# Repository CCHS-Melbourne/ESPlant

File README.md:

ESPlant - Environment Sensor Plant
=============

Welcome to the linux.conf.au Open Hardware Project.  You can see information about this and other MiniConfs at http://www.openhardwareconf.org/wiki/Main_Page

The ESPlant kit is designed to provide an open source platform to transmit environmental data to a central source using the power of wifi.

Assembled PCB:

Prototype board in action (before significant changes):

Check out a video of pick-n-placing components of the boards you'll be getting at LCA 2016.
https://www.youtube.com/watch?v=282qku2C4xo

FEATURES
--------

* ESP8266 WiFi enabled microcontroller. You can program it via the Arduino IDE, or alternatively Espressif SDK or esp-open-rtos.
* Secondary microcontroller (STM32F042) acts as USB/Serial interface and i2c Analog to Digital Converter
* Battery holder for 16340 sized 3.7V lithium cell
* Lithium battery charger interface (solar input friendly)
* Board automatically switches power source between solar input, battery, and USB power as applicable.

## Onboard Sensors (on I2C bus)

* BME280 Temperature/Humidity/Barometric Pressure sensor
* ADXL345 accelerometer

## External Sensors (all optional, connected to screw terminals)

* 2x soil moisture sensors (via ADC pins)
* DS18B20 connected to GPIO 12.
* PIR (infrared motion) sensor connected to GPIO 15.
* WS2812B LED strip connected to GPIO 13 (mislabelled as 15 on V1.3 PCB!)

The 3.3V "VSens" power rail is switchable on/off by the microcontroller. It defaults to unpowered (off). The GPIO to use is 14, and it is active low (ie driving the output low turns VSens on, driving it high turns it off).

Assembly Steps
--------------

[Assembly guide on the wiki](https://github.com/CCHS-Melbourne/ESPlant/wiki/Step-1:-Step-by-Step-Assembly).

Using with Arduino
------------------

To add ESP8266 support to the Arduino IDE (1.6.6 or newer) we use the external [ESP8266 Arduino](https://github.com/esp8266/Arduino) project. We need the *staging version* not the stable version of the ESP8266 support package.

Follow these steps to install:

* Install Arduino 1.6.6 or newer (1.6.7 is fine) from the [Arduino website](http://arduino.cc).
* Start Arduino IDE and open Preferences window.
* Enter `http://arduino.esp8266.com/staging/package_esp8266com_index.json` into Additional Board Manager URLs field. You can add multiple URLs, separating them with commas.
* From the Tools menu choose Board -> Board Manager
* A window will open. Search for ESP8266.
* Choose a version from the drop-down in the bottom right. There will probably only be one shown there.
* Click Install

Connecting ESPLant to your computer
-----------------------------------

* No drivers required on Linux, OS X, or Windows 10.
* No manual reset or button pressing dance required to program.
* In [ESP8266 Arduino IDE](https://github.com/esp8266/arduino), under Tools menu, set Board to "NodeMCU V1.0" (fully compatible).
* Can set upload speed to 230400. 460800 works in most cases (you might get occasional failures at 460800)

Getting ESPlant
---------------

You need to clone the ESPlant repo from github, using the `--recursive` option to pick up submodules. If you download a zip file then the submodule parts will be missing, so we recommend using git to get it.

The command is:
```
git clone --recursive https://github.com/CCHS-Melbourne/ESPlant
```

Libraries you will need
-----------------------

Arduino uses libraries to work with additional hardware or software functionality in an easy way. Normally you can download and install libraries directly inside the Arduino IDE by choosing Sketch menu -> Include Library -> Manage Libraries.

**One library that you should install this way is the OneWire library**. Search for "OneWire" and then click the Install button to install it.

For the ESPlant the other required libraries are set up as "git submodules" inside the "Libraries" directory. If you did a "recursive" clone then you will have these, otherwise you can add them to a "normal" clone by running this command:

```
git submodule update --init
```

Inside the Libraries directory there is a script `install_libraries.sh` that you can run on Linux or OS X to symlink all of the libraries into your Arduino libraries directory so you can use them.

```
cd Libraries
./install_libraries.sh
```

On Windows you'll need to copy all the subdirectories of the libraries directory (copy them into the My Documents/Arduino/libraries directory).

The one Library here that is part of this repo (not a submodule) is the "ESP_Kwai" library that acts as a bridge to the peripheral hardware.

Don't forget OneWire as well (see above).

Upload your first program ("sketch")
------------------------------------

After restarting Arduino IDE to pick up the new libraries, you're ready to upload your first program (Arduino calls them "sketches"):

* Choose File->Open in Arduino and open the `Firmware/ESPlant_serial_sensor` from this repository. This is a simple sketch that outputs all the analog values read by the board.
* Press the "Upload" button to send it to your board. Watch for messages indicating the upload was successful.
* Open the serial monitor (under Tools) and set the baud rate to 115200 in order to watch the output from the sketch.

Other Sketches to Try
---------------------

The repo includes the following sketches:

* `ESPlant_prodtest` is the hardware production test. It tests all the sensors to confirm the hardware is good. There are instructions in a large comment at the top of the sketch. You can run this if you think you're having hardware problems, or to look at example code for any individual point.

* `ESPlant_MQTT_sensor` uses MQTT to push data to a server. It includes easy provisioning mechanisms for connecting to the WiFi. It has [other instructions in its README file](https://github.com/CCHS-Melbourne/ESPlant/tree/master/Firmware/ESPlant_MQTT_sensor#readme) for WiFi configuration.

Where to Now?
-------------

Check out (and contribute to) [the wiki](https://github.com/CCHS-Melbourne/ESPlant/wiki). There is a pinout summary, sensor summary, power information, etc.

Onboard STM32
-------------

There is an onboard STM32 microcontroller that acts as USB/Serial converter and an i2c connected ADC (Analog/Digital Converter) device.

For the i2c functionality, the `ESP_Kwai` library (under Libraries/ESP_Kwai) acts as a bridge (*get it*) to the i2c ADC peripherals on the ESPlant. It can automatically read all the values connected to the ADC and return them.

If you want more information on how the STM32 works internally, check out the [README in the STM_Firmware directory](https://github.com/CCHS-Melbourne/ESPlant/tree/master/STM_Firmware#readme).

CREDITS
------------

This project was designed by the 2016 linux.conf.au Open Hardware Team!
 - [John Spencer](https://github.com/mage0r)
 - [Angus Gratton](https://github.com/projectgus)
 - [Andy Gelme](https://github.com/geekscape)
 - [Jon Oxer](https://github.com/jonoxer)
 - [Mark Wolfe](https://github.com/wolfeidau)

Made at hackmelbourne.org!

SPECIAL THANKS
------------

To the HackMelbourne (CCHS, http://hackmelbourne.org) community of Melbourne, Australia.

To all other open-source developers whose countless hours supported every other aspect of this design.

DISTRIBUTION
------------
The specific terms of distribution of this project are governed by the
license referenced below. Please contact the copyright owner if you wish to modify the board for distribution. Please utilize this design for personal or research projects. Please acknowledge all contributors.

LICENSE
-------
Licensed under the TAPR Open Hardware License (www.tapr.org/OHL).
The "license" sub-folder also contains a copy of this license in plain text format.

Copyright John Spencer, Angus Gratton, Andy Gelme, Jon Oxer 2015

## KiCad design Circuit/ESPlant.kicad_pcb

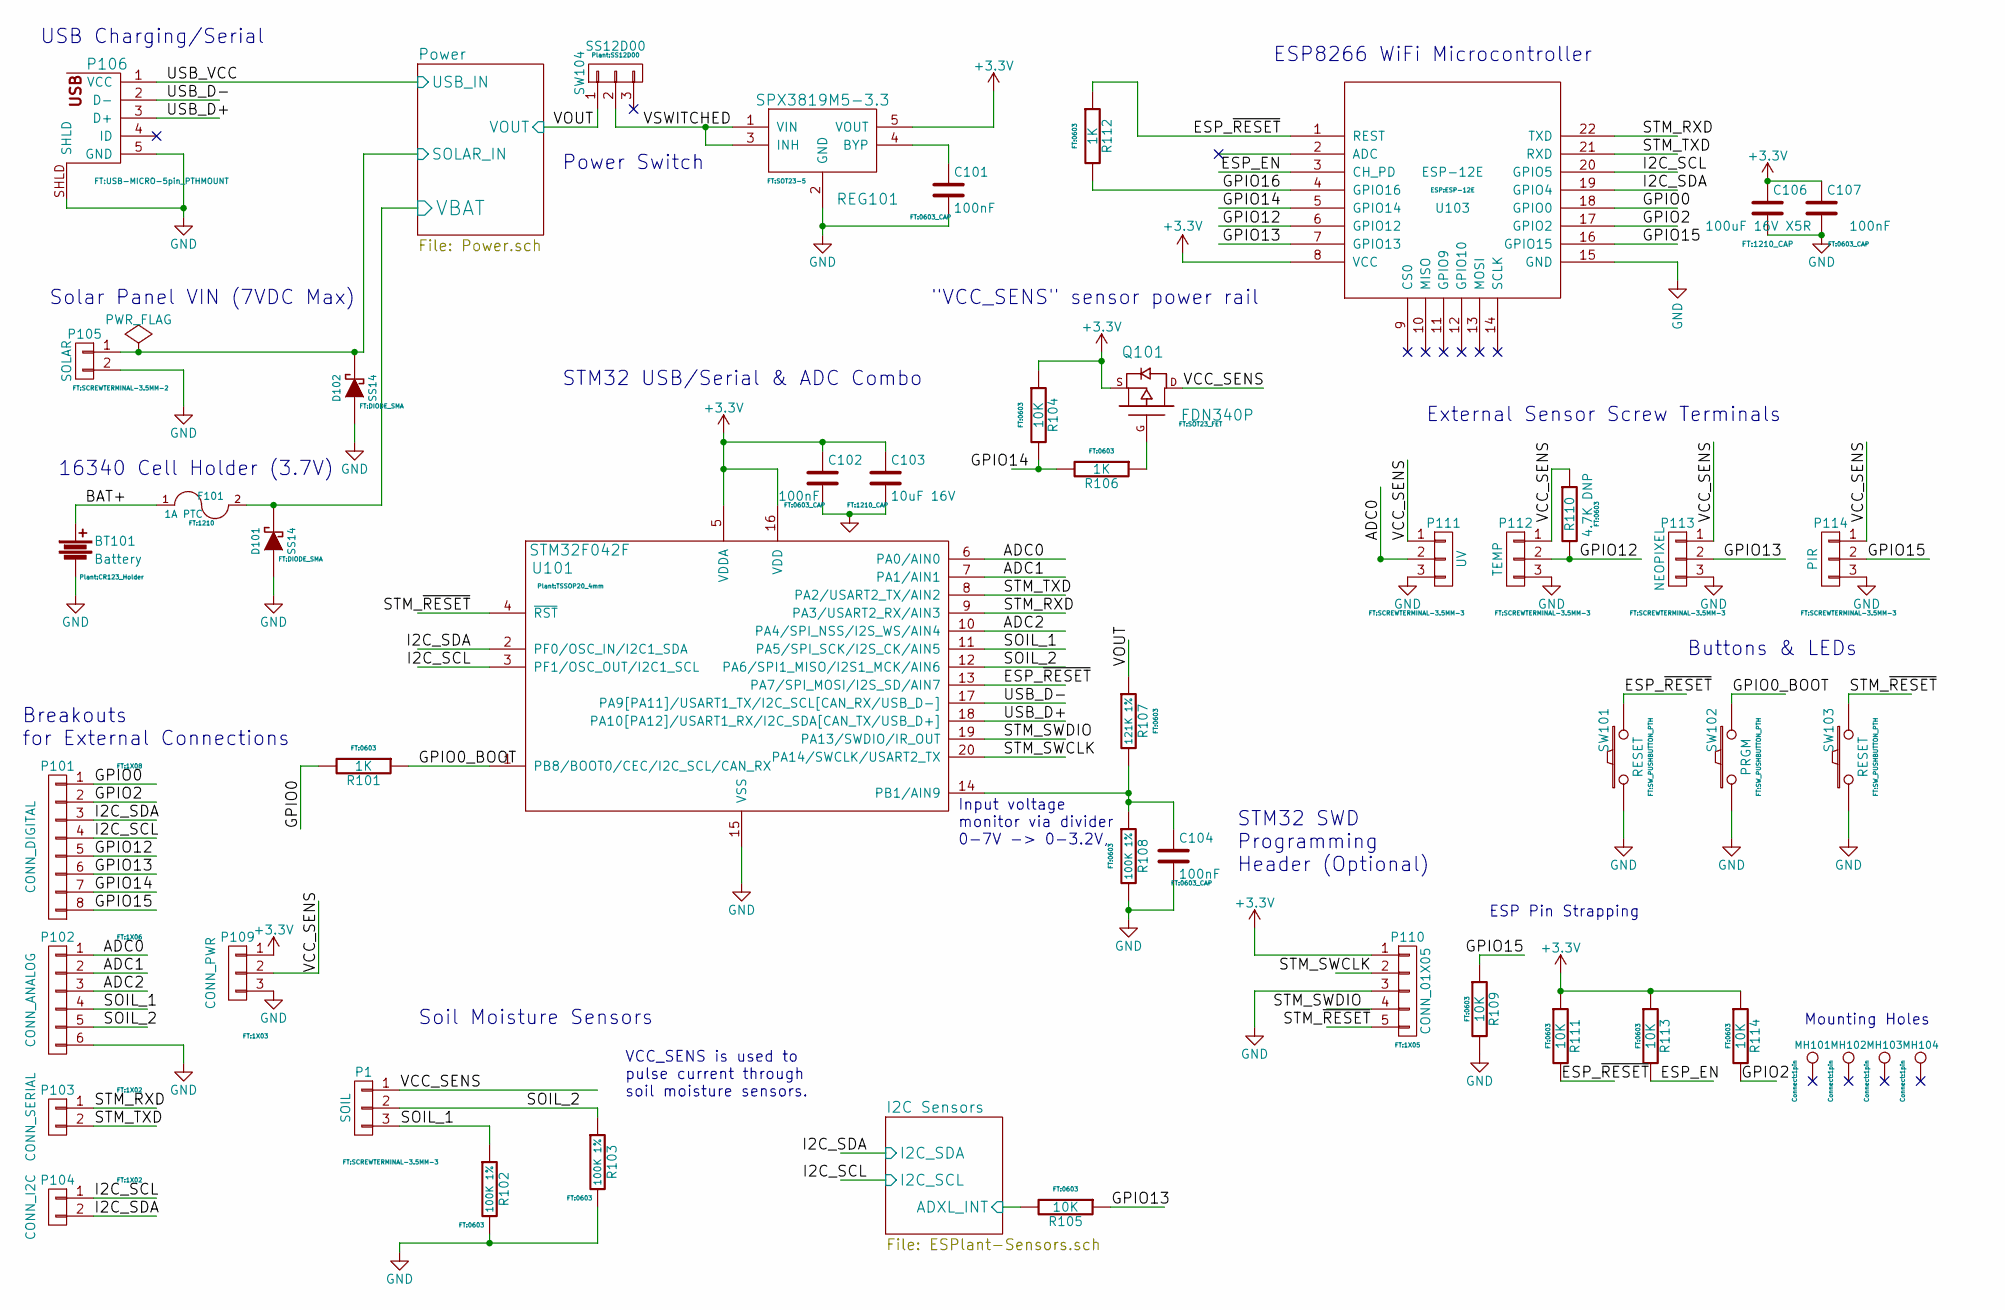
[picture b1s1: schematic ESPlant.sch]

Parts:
BT101: Battery; CR123_Holder
C101, C102, C104, C107: 100nF; 0603_CAP
C103: 10uF 16V; 1210_CAP
C106: 100uF 16V X5R; 1210_CAP
D101, D102: SS14; DIODE_SMA
F101: 1A PTC; 1210
MH101, MH102, MH103, MH104: TEST_1P; 1pin
P1: SOIL; SCREWTERMINAL-3.5MM-3
P101: CONN_DIGITAL; 1X08
P102: CONN_ANALOG; 1X06
P103: CONN_SERIAL; 1X02
P104: CONN_I2C; 1X02
P105: SOLAR; SCREWTERMINAL-3.5MM-2
P106: USB_5PIN_SHELL; USB-MICRO-5pin_PTHMOUNT
P109: CONN_PWR; 1X03
P110: CONN_01X05; 1X05
P111: UV; SCREWTERMINAL-3.5MM-3
P112: TEMP; SCREWTERMINAL-3.5MM-3
P113: NEOPIXEL; SCREWTERMINAL-3.5MM-3
P114: PIR; SCREWTERMINAL-3.5MM-3
Q101: FDN340P; SOT23_FET
R101, R106, R112: 1K; 0603
R102, R103, R108: 100K 1%; 0603
R104, R105, R109, R111, R113, R114: 10K; 0603
R107: 121K 1%; 0603
R110: 4.7K DNP; 0603
REG101: SPX3819M5-3.3; SOT23-5
SW101, SW103: RESET; SW_PUSHBUTTON_PTH
SW102: PRGM; SW_PUSHBUTTON_PTH
SW104: SS12D00
U101: STM32F042F; TSSOP20_4mm
U103: ESP-12E

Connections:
+3V3: C102.1, C103.1, C106.1, C107.1, P109.1, P110.1, Q101.S, R104.1, R111.1, R113.1, R114.1, REG101.5 (VOUT), U101.5 (VDDA), U101.16 (VDD), U103.8 (VCC); also elsewhere on the board
/ADC0: P102.1, P111.2, U101.6 (PA0/AIN0)
/ADC1: P102.2, U101.7 (PA1/AIN1)
/ADC2: P102.3, U101.10 (PA4/SPI_NSS/I2S_WS/AIN4)
/BAT+: BT101.1, F101.1
/ESP_EN: R113.2, U103.3 (CH_PD)
/ESP_~RESET: R111.2, R112.1, SW101.2, U101.13 (PA7/SPI_MOSI/I2S_SD/AIN7), U103.1 (REST)
/GPIO0: P101.1, R101.2, U103.18 (GPIO0)
/GPIO0_BOOT: R101.1, SW102.2, U101.1 (PB8/BOOT0/CEC/I2C_SCL/CAN_RX)
/GPIO2: P101.2, R114.2, U103.17 (GPIO2)
/GPIO12: P101.5, P112.2, R110.2, U103.6 (GPIO12)
/GPIO13: P101.6, P113.2, R105.1, U103.7 (GPIO13)
/GPIO14: P101.7, R104.2, R106.2, U103.5 (GPIO14)
/GPIO15: P101.8, P114.2, R109.1, U103.16 (GPIO15)
/GPIO16: R112.2, U103.4 (GPIO16)
/I2C Sensors/ADXL_INT: R105.2; also elsewhere on the board
/I2C Sensors/I2C_SCL: P101.4, P104.1, U101.3 (PF1/OSC_OUT/I2C1_SCL), U103.20 (GPIO5); also elsewhere on the board
/I2C Sensors/I2C_SDA: P101.3, P104.2, U101.2 (PF0/OSC_IN/I2C1_SDA), U103.19 (GPIO4); also elsewhere on the board
/Power/SOLAR_IN: D102.K, P105.1; also elsewhere on the board
/Power/USB_IN: P106.1 (VCC); also elsewhere on the board
/Power/VBAT: D101.K, F101.2; also elsewhere on the board
/Power/VOUT: R107.1, SW104.1; also elsewhere on the board
/SOIL_1: P1.3, P102.4, R102.1, U101.11 (PA5/SPI_SCK/I2S_CK/AIN5)
/SOIL_2: P1.2, P102.5, R103.1, U101.12 (PA6/SPI1_MISO/I2S1_MCK/AIN6)
/STM_RXD: P103.1, U101.9 (PA3/USART2_RX/AIN3), U103.22 (TXD)
/STM_SWCLK: P110.2, U101.20 (PA14/SWCLK/USART2_TX)
/STM_SWDIO: P110.4, U101.19 (PA13/SWDIO/IR_OUT)
/STM_TXD: P103.2, U101.8 (PA2/USART2_TX/AIN2), U103.21 (RXD)
/STM_~RESET: P110.5, SW103.2, U101.4 (~RST)
/USB_D+: P106.3 (D+), U101.18 (PA10[PA12]/USART1_RX/I2C_SDA[CAN_TX/USB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)
/USB_D-: P106.2 (D-), U101.17 (PA9[PA11]/USART1_TX/I2C_SCL[CAN_RX/USB_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)
/VCC_SENS: P1.1, P109.2, P111.1, P112.1, P113.1, P114.1, Q101.D, R110.1
/VSWITCHED: REG101.1 (VIN), REG101.3 (INH), SW104.2
GND: BT101.2, C101.2, C102.2, C103.2, C104.2, C106.2, C107.2, D101.A, D102.A, P102.6, P105.2, P106.5 (GND), P106.SHLD, P109.3, P110.3, P111.3, P112.3, P113.3, P114.3, R102.2, R103.2, R108.2, R109.2, REG101.2 (GND), SW101.1, SW102.1, SW103.1, U101.15 (VSS), U103.15 (GND); also elsewhere on the board
unnamed: C101.1, REG101.4 (BYP)
unnamed: C104.1, R107.2, R108.1, U101.14 (PB1/AIN9)
unnamed: Q101.G, R106.1

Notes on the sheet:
USB Charging/Serial
Solar Panel VIN (7VDC Max)
16340 Cell Holder (3.7V)
Input voltage monitor via divider 0-7V -> 0-3.2V,
ESP Pin Strapping
STM32 USB/Serial & ADC Combo
ESP8266 WiFi Microcontroller
Buttons & LEDs
Breakouts for External Connections
Soil Moisture Sensors
VCC_SENS is used to pulse current through soil moisture sensors.
STM32 SWD Programming Header (Optional)
"VCC_SENS" sensor power rail
External Sensor Screw Terminals
Mounting Holes
Power Switch

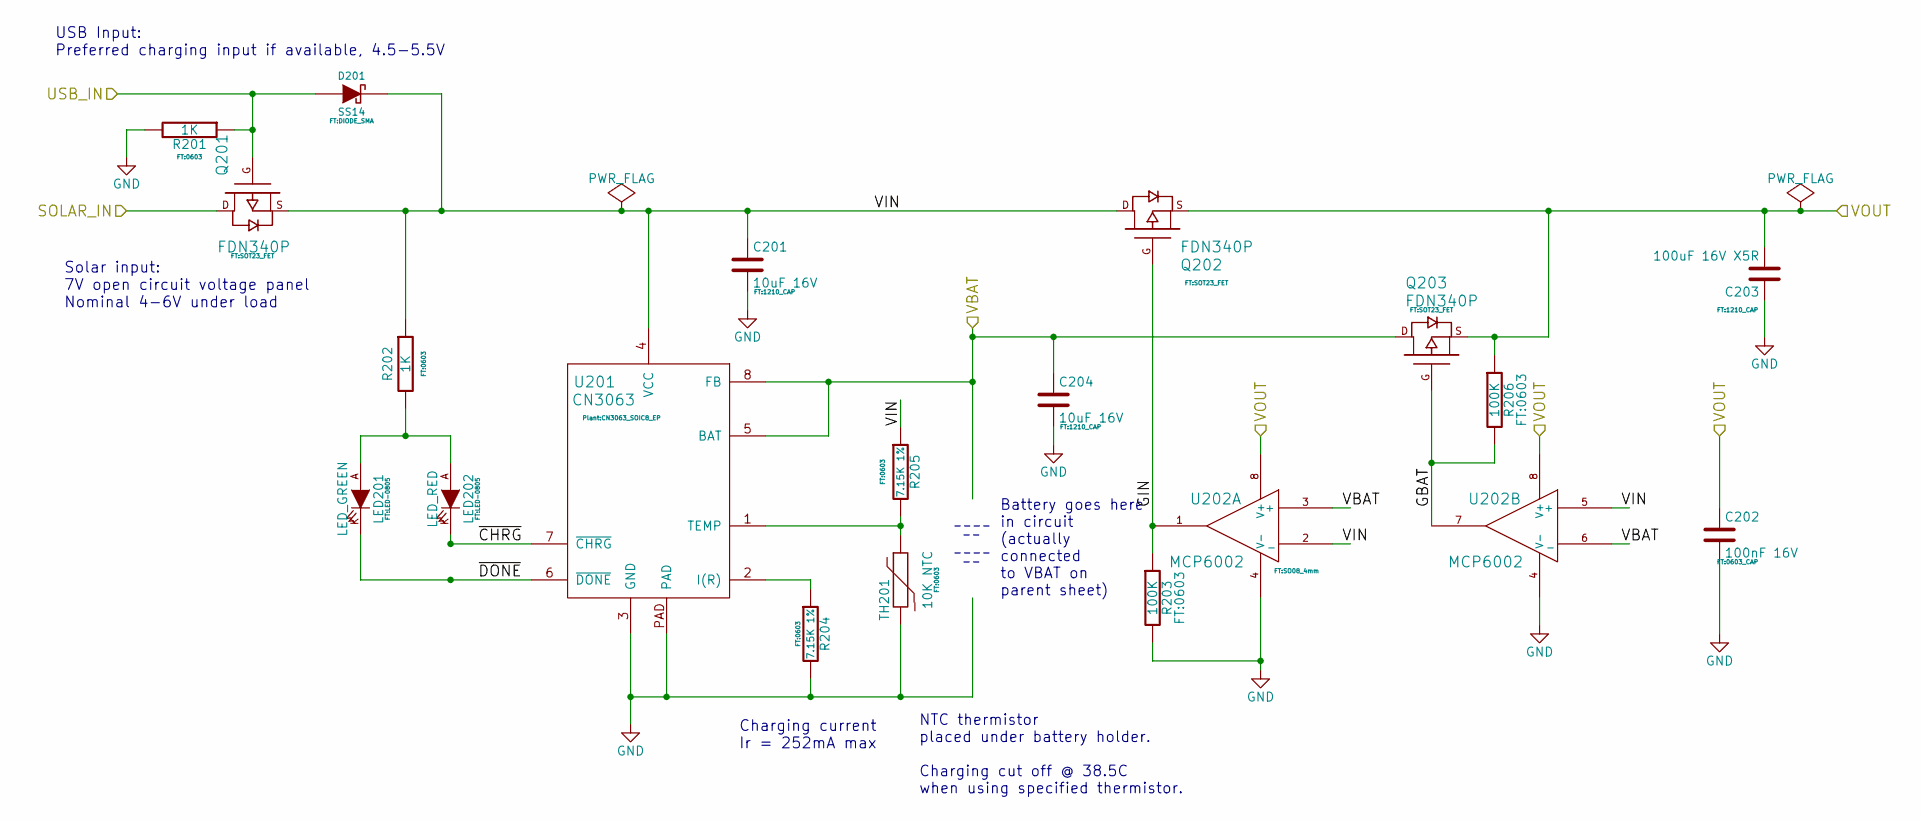
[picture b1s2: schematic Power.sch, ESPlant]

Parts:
C201, C204: 10uF 16V; 1210_CAP
C202: 100nF 16V; 0603_CAP
C203: 100uF 16V X5R; 1210_CAP
D201: SS14; DIODE_SMA
LED201: LED_GREEN; LED-0805
LED202: LED_RED; LED-0805
Q201, Q202, Q203: FDN340P; SOT23_FET
R201, R202: 1K; 0603
R203, R206: 100K; 0603
R204, R205: 7.15K 1%; 0603
TH201: 10K NTC; 0603; MPN NCP18XH103F03RB
U201: CN3063; CN3063_SOIC8_EP
U202: MCP6002; SO08_4mm

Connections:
/Power/GBAT: Q203.G, R206.2, U202.7
/Power/GIN: Q202.G, R203.1, U202.1
/Power/SOLAR_IN: Q201.D; also elsewhere on the board
/Power/USB_IN: D201.A, Q201.G, R201.1; also elsewhere on the board
/Power/VBAT: C204.1, Q203.D, U201.5 (BAT), U201.8 (FB), U202.3 (+), U202.6 (_); also elsewhere on the board
/Power/VIN: C201.1, D201.K, Q201.S, Q202.D, R202.1, R205.1, U201.4 (VCC), U202.2 (_), U202.5 (+)
/Power/VOUT: C202.1, C203.2, Q202.S, Q203.S, R206.1, U202.8 (V+); also elsewhere on the board
/Power/~CHRG: LED202.K, U201.7 (~CHRG)
/Power/~DONE: LED201.K, U201.6 (~DONE)
GND: C201.2, C202.2, C203.1, C204.2, R201.2, R203.2, R204.2, TH201.2, U201.3 (GND), U201.PAD, U202.4 (V-); also elsewhere on the board
unnamed: LED201.A, LED202.A, R202.2
unnamed: R204.1, U201.2 (I(R))
unnamed: R205.2, TH201.1, U201.1 (TEMP)

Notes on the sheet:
USB Input: Preferred charging input if available, 4.5-5.5V
Solar input: 7V open circuit voltage panel Nominal 4-6V under load
Charging current Ir = 252mA max
Battery goes here in circuit (actually connected to VBAT on parent sheet)
NTC thermistor placed under battery holder. Charging cut off @ 38.5C when using specified thermistor.

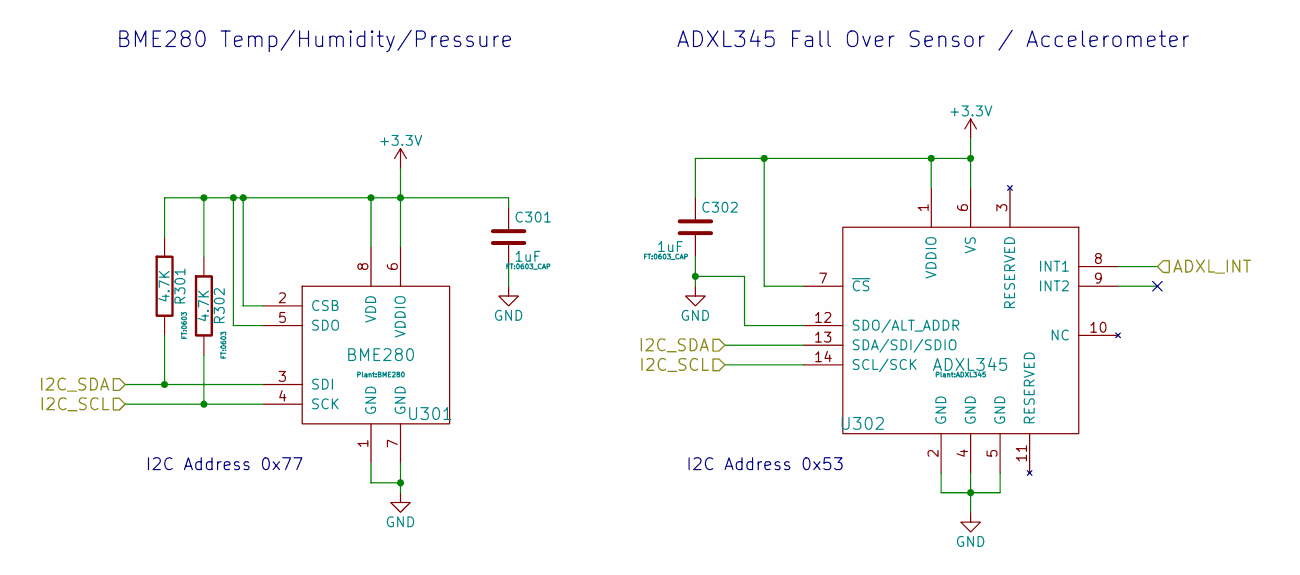
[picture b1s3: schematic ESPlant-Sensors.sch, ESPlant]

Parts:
C301, C302: 1uF; 0603_CAP
R301, R302: 4.7K; 0603
U301: BME280
U302: ADXL345

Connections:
+3V3: C301.1, C302.1, R301.1, R302.1, U301.2 (CSB), U301.5 (SDO), U301.6 (VDDIO), U301.8 (VDD), U302.1 (VDDIO), U302.6 (VS), U302.7 (~CS); also elsewhere on the board
/I2C Sensors/ADXL_INT: U302.8 (INT1); also elsewhere on the board
/I2C Sensors/I2C_SCL: R302.2, U301.4 (SCK), U302.14 (SCL/SCK); also elsewhere on the board
/I2C Sensors/I2C_SDA: R301.2, U301.3 (SDI), U302.13 (SDA/SDI/SDIO); also elsewhere on the board
GND: C301.2, C302.2, U301.1 (GND), U301.7 (GND), U302.2 (GND), U302.4 (GND), U302.5 (GND), U302.12 (SDO/ALT_ADDR); also elsewhere on the board

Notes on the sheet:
I2C Address 0x77
BME280 Temp/Humidity/Pressure
I2C Address 0x53
ADXL345 Fall Over Sensor / Accelerometer

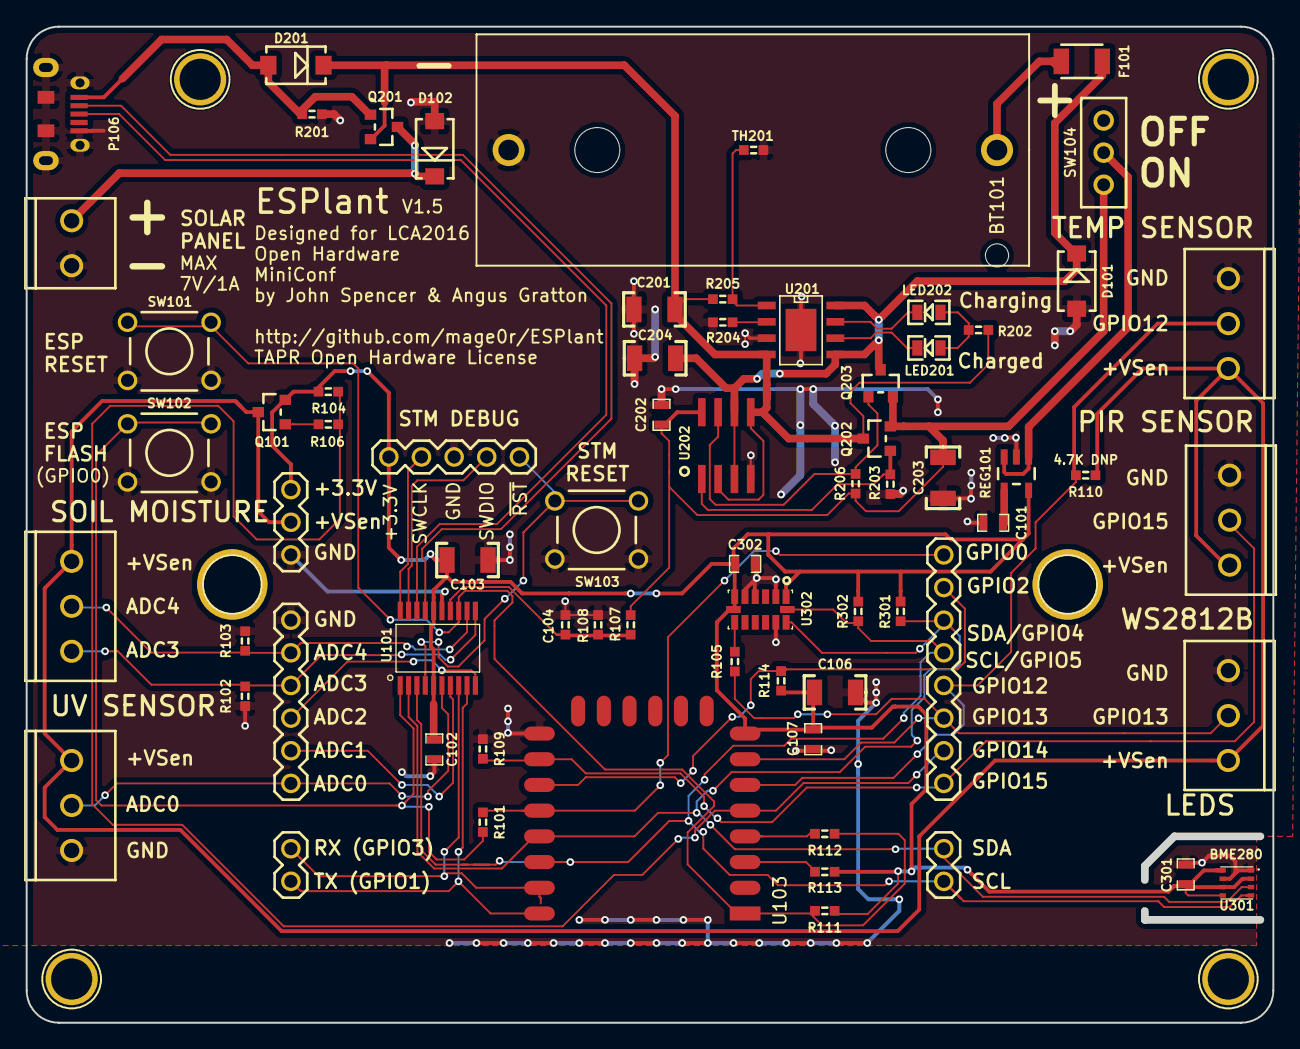
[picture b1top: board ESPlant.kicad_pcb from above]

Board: 2 copper layers, 97.0 x 77.5 mm, 76 parts (0 on the bottom side), 45 nets.

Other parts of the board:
1pin, 1pin#2: VAL**; 1pin

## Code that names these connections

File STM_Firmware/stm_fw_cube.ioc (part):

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Mcu.Name=STM32F042F4Px
Mcu.Package=TSSOP20
Mcu.UserName=STM32F042F4Px
PA0.Mode=IN0
PA0.Signal=ADC_IN0
PA1.Mode=IN1
PA1.Signal=ADC_IN1
PA11.Mode=Device
PA11.Signal=USB_DM
PA12.Mode=Device
PA12.Signal=USB_DP
PA13.Mode=Serial-WireDebug
PA13.Signal=SYS_SWDIO
PA14.Mode=Serial-WireDebug
PA14.Signal=SYS_SWCLK
PA2.Mode=Asynchronous
PA2.Signal=USART2_TX
PA3.Mode=Asynchronous
PA3.Signal=USART2_RX
PA4.Mode=IN4
PA4.Signal=ADC_IN4
PA5.Mode=IN5
PA5.Signal=ADC_IN5
PA6.Mode=IN6
PA6.Signal=ADC_IN6
PA7.Mode=IN7
PA7.Signal=ADC_IN7
PB1.Mode=IN9
PB1.Signal=ADC_IN9
PB8.Signal=GPIO_Input
PF0-OSC_IN.GPIOParameters=GPIO_PuPdOD
PF0-OSC_IN.GPIO_PuPdOD=GPIO_NOPULL
PF0-OSC_IN.Mode=I2C
PF0-OSC_IN.Signal=I2C1_SDA
PF1-OSC_OUT.GPIOParameters=GPIO_PuPdOD
PF1-OSC_OUT.GPIO_PuPdOD=GPIO_NOPULL
PF1-OSC_OUT.Mode=I2C
PF1-OSC_OUT.Signal=I2C1_SCL
RCC.SYSCLKFreq_VALUE=48000000
RCC.SYSCLKSource=RCC_SYSCLKSOURCE_HSI48
board=stm_fw_cube

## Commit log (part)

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2015-11-02 :neckbeard: Added .gitattributes
2015-11-02 Basic Readme to get started
2015-11-02 Initial commit of basic components
    Include the esp and a bunch of fun stuff like battery and LED's.
2015-11-02 Worst mock up ever
2015-11-02 Yep, I keep changing copy.
2015-11-02 Added UFQFPN48 footprint
2015-11-02 Updated UFQFPN48 Footprint
2015-11-10 Add Freetronics KiCAD library as submodule
2015-11-10 Updated Lithium power circuit
2015-11-10 Updated to use esp12e
2015-11-10 Updated kicad library to submodule
2015-11-10 Cleaned up directory.
2015-11-11 Change battery switching circuit to use MCP6002 comparator instead
2015-11-11 Remove invalid git submodule entry for esp8266
2015-11-11 Add input cap to solar input
2015-11-11 Remove accidental 'power' project file
2015-11-18 Flesh out schematic sensor elements, etc.
2015-11-20 Downgrade STM32 to cute little TSSOP20 STM32F042F6
2015-11-26 Schematic last touches
    Added:
    Breakouts for individual sensors.
    Breakouts for all pins.
    ESP controllable power.
    Replaced Battery FET with Fuse.
    Removed D13 LED.
2015-11-27 Rename RAIL_VCC to VCC_SENS, add pullup and gate current resistor to FET
2015-11-27 Footprint assignment for schematic, including footprints for new parts
    Removed on-PCB UV sensor in favour of offboard one.
2015-11-27 Updated footprints for connectors
    Removed Surplus power.
    Added connectors for soil sensor.
2015-11-28 Fuse missing connection
2015-11-29 Fixed Charge LED's
    They were accidentally linked.
2015-11-29 First cut routing
2015-11-29 Better routing pass
2015-11-29 Shrink back ground plane slots some more
2015-11-30 Routing finished?
2015-11-30 Add crowbar diode for solar panel polarity protection
2015-12-09 Barebones STM project
2015-12-10 STM firmware: Can RX data from ESP8266
2015-12-10 Add support for I2C ADC interface, untested so far
2015-12-12 STM FW: Disable BOOT0 pin on first run
2015-12-12 STM firmware: Working ESP auto-reset for programming, behaviour matches NodeMCU board
    When programming with Arduino IDE, choose NodeMCU in board type.
2015-12-12 Revise schematic for V1.1 based on V1.0 evaluation:
    * Swap SDA, SCL on ESP (5,4 to 4,5) to match Arduino default
    * Q101 source, drain were swapped
    * BME280 change i2c address config 0x76 -> 0x77 (match Adafruit library)
    * ADXL345 change i2c address from 0x1d -> 0x53 (match Adafruit library)
    * Specify colours for "charging", "done" LEDs in component values
    * R202, R203 LED series resistors changed to 1K
2015-12-12 STM I2C/ADC functions - Currently kind of broken (I2C slave event causes infinite interrupts).
    Has all the ingredients of something that will work, though :)
2015-12-12 10x5 PCB design.
2015-12-12 5 Vias, no text.
2015-12-12 Traces in.
2015-12-12 Added text.
2015-12-12 Fixed Readme
2015-12-12 Adding photo of actual boards.
2015-12-12 Updated the silkscreen text
2015-12-12 Updates to silkscreen.
2015-12-13 Changes made elsewhere. Probably a mess.
    Fix battery footprint.
    Add charging labels.
    Duplicate & flip TH labels.
2015-12-13 Remove backup Kicad files from repo
2015-12-13 Downsize 0805s to 0603 for @jonoxer's pnp machine :)
2015-12-13 V1.1 reroutes, excluding 0805->0603
2015-12-14 Shrink to 0603, some other cleanups
2015-12-14 Add cable tie holes, V1.1 production candidate?
2015-12-15 Add LCA Geelong wave logo to back of V1.1 PCB
    Thanks to @rdpowers for the idea and @dtbell91 for providing a logo at
    short notice.
2015-12-15 Battery is a 16340 cell not an 18340 cell
2015-12-15 Tweak fuse a little further away from power switch body (being paranoid)
2015-12-15 Add NTC thermistor for overtemperature charging cutoff
2015-12-15 Combine series resistors on CN3063 CHRG/DONE, thanks @GeoffLethbridge for the tip
2015-12-15 Regenerate schematic PDF for V1.1
2015-12-15 Add capacitor on VBAT, mitigate oscillation at end of charge
    Because VBAT was otherwise disconnected when charging finished, the
    voltage oscillated from charge/done/charge a lot.
2015-12-15 Second go at a layout.
2015-12-16 More Photos.
2015-12-16 Adding images
2015-12-21 Added renders to main page.
2015-12-28 Fixed bad merge
2015-12-28 More Merge Conflicts
2015-12-28 Ok, all updated I hope
2015-12-30 Add barebones sensortest sketch
2015-12-30 Fix stray n/c trace, ground CN3063 pad, bump to V1.2
2015-12-30 Fix silkscreen & slot width issues noted by @hackvana, bump version V1.3
2015-12-30 Update ground plane from DRC
2015-12-30 Add bulk capacitor on VBAT, mitigate oscillation at end of charge
    Because VBAT was otherwise disconnected when charging finished meaning
    with very low capacitance, the voltage oscillated from charge/done/charge.
2015-12-30 Add feature summary to README
2015-12-30 Fix labelling of 'WS2812B' screw terminal as GPIO15, is actually GPIO13
2016-01-04 i2c ADC almost working
2016-01-04 Add -g to linker args, keep debugging info when LTO is on
2016-01-04 i2c ADC working at a very basic level
2016-01-05 i2c ADC working
2016-01-10 Updated Photo of Prototype in action.
2016-01-13 Add DS18B20 offboard temp sensor to test sketch
2016-01-13 Hack to fix the problem where i2c can make USB stop sending data for a while
    It seems like there's a circumstance where i2c interaction "breaks"
    USB (some event is skipped and then no UART data gets sent until later
    on when the buffer is full.)
    The hacky fix for this is making I2C lower priority than USB. The
    problem with this fix is that sometimes (when receiving CDC data from
    the host) the USB can spend a while in its interrupt handler, which
2016-01-13 Drop test sketch delay period, quicker results
2016-01-13 STM32 Firmware major cleanup - remove cruft, rearrange, add README
2016-01-13 STM32 Firmware: Add license
2016-01-13 Rearrange licenses to better meet the pid.codes terms and make it clearer which license applies where
2016-01-13 README: Add some notes about using with Arduino
2016-01-14 Adding more how to build photos
2016-01-20 Added initial version of the mqtt logging firmware.
2016-01-20 Add beginnings of final hardware tester
2016-01-20 Version of prodtest used for first 12 boards last night
    (Disabled UV sensor due to failed to get a reading indoors, disabled
    IR sensor due to not working at 3.3V.)
2016-01-21 Prodtest: Add tests for NeoPixels, PIR
2016-01-21 Prodtest: Add comment about test procedure
2016-01-22 Use WFI sleep mode (least intrusive sleep mode) instead of busy-looping
2016-01-22 Add note about VSens rail
2016-01-23 Don't reset ESP when STM resets, avoid problems with brownout reset loops
2016-01-23 USB: Stop UART/TIM3 clocks when USB CDC disconnected
2016-01-23 Code changes to use STOP mode: Currently doesn't wake up properly
2016-01-23 Working STOP mode, low power OK but not great
    Whole board down to 4.4mA when ESP8266 is asleep. Odd thing is this drops
    to 2.1mA immediatel after STM32 is reset.
    Cause appears to be writing to ADC channels (from ADC_CHANNEL[3] and up),
    even if the channels are being disabled not enabled. Not clear what the
    real cause is yet.
    Lots of workarounds in code now, none of which appear to have a large impact.
2016-01-24 Adding Assembly Photos
2016-01-27 Fixup prodtest sketch with input from Thomas
2016-01-27 STM FW: Defer ADC start until end of initial i2c transaction
2016-01-27 STM FW: Update VID/PID, use serial number descriptor for versioning
    Thanks @pidcodes for providing this community service. As per http://pid.codes/1209/9021/
2016-01-27 STM FW: Remove as much boilerplate cruft as possible
2016-01-27 STM FW: Rename to esplant_stm_fw
2016-01-27 Fix concurrent STOP mode and USB support
2016-01-27 STM: Flush TXDR register if we have no i2c data to send
    Fixes (1) of #3, now power on idle current is down to 1.1mA same as on reset.
2016-01-27 Updated ESP firmware to add most of the sensors.
    * Added support for the i2c to ADC bridge which is called Kwai
    * Added support for one wire to read the external soil tempreture sensor.
    * Renamed some of the topics.
2016-01-27 Added ESP Kwai library which bridges I2C from ESP to ARM for ADCs.
2016-01-27 STM: Sanitise resetting of i2c bus
    Don't need it on sleep (makes no difference)
    When TIMEOUT occurs, ref manual says to sleep at least 4 APB ticks before un-resetting
2016-01-27 STM Makefile: flash target should exit after flashing
2016-01-27 STM FW: Version 0.2
2016-01-27 STM: Change TXD flush mechanism yet again
2016-01-29 Removing all these huge images
2016-01-29 Changed to using secure client.
2016-01-30 Replace renders on README with a board photo
2016-01-30 Reword README picture captions
2016-01-30 Minor visual clean up on power schematic
2016-01-30 Updated Link to Plant Sensor Libraries
2016-01-30 Updated with Libraries that are requried
2016-01-30 Fixed spacing
2016-01-30 Text Update
2016-01-30 Update README.md to include required Adafruit Unified Sensor Driver
2016-01-30 Fix number of LEDs in NeoPixel ring
2016-01-31 README improvements, STM Makefile tweaks
2016-01-31 Rename ESPlant_sensor.ino to ESPlant_MQTT_sensor.ino
2016-01-31 Add install_libraries.sh script to add all new libraries to Arduino folder
2016-01-31 Make git submodules for all third party libraries
2016-01-31 Add some comments and a default pin number for ESP_Kwai
2016-01-31 Rename install_modules.sh to install_libraries.sh
2016-01-31 Update install_libraries.sh script to work on OS X with no realpath
2016-01-31 Rejigged this and made TLS optional as well as updating README.
2016-01-31 Fix bug with install_libraries path detection
2016-01-31 ESP_Kwai: Rename battery_voltage to input_voltage, use millivolts as unit
2016-01-31 ESP_Kwai: Replace array of channel values with an enum, expose read_adc method for single channel reads
2016-01-31 ESP_Kwai: Call Wire.begin() as part of begin()
2016-01-31 Fix compile error in ESP_Kwai.begin()
2016-01-31 ESP_Kwai Use the Arduino "single class" model
2016-01-31 Update ESP_Onboarding submodule
2016-01-31 Add new ESPlant_serial_sensor.ino sketch
2016-01-31 Harmonise READMEs, add staging instructions to main README
2016-01-31 Just some tweaks to the readme to fix quotes.
2016-01-31 Update MQTT README
2016-01-31 README: Add note about OneWire
2016-01-31 Change the git submodule url for the FT kicad library
2016-01-31 Use 'git submodule update .' to avoid errors if Circuit submodule fails
2016-02-01 Add Adafruit's neopixel to the set of library submodules
2016-02-01 Added neopixel streaming LED with color picker to random new color.
    Color code is super configurable:
    - how quickly you change from one color to the next (next target color
    is picked randomly)
    - how many steps of intermediate colors you get between color A and color B
    - how long you stay on color B before picking a new color
    - how many trailing LEDs of previous colors get displayed
2016-02-01 Fix color changing to set LED even if LED color didn't change.
    (because we could have changed to another LED by then).
    Also adjust led trail and timing.
2016-02-01 Speed up and lenghten LED trail.
2016-02-01 Improve output of values.
    re-ordered values by type (temps together, volts together, etc...)
    Added output of solar panels (use a voltage divider, connect to ADC2)
    Also added units for each output.
2016-02-01 Add new MQTT sensor sketch that uses deep sleep mode
2016-02-01 Add a constant for how long to sleep for
2016-02-02 Made PV output voltage an ifdef since it's not supported by default hw.
2016-02-02 Improved documentation.
2016-02-02 Re-organized logging output by type and with units added.
2016-02-08 Small cleanups, added support for changing LED trail length and speed.
    - RGB_LED_BRIGHTNESS is now controlled by the first soil tester
    - RGB_LED_TRAIL (and speed) is also now controlled by the 2nd soil tester
    - added support for motion detector (which turns on the LEDs) (define
    FIXED_MOTION_SENSOR)
2016-02-20 README: Explain git clone requirements, only way to get submodules
    Thanks to @RobynWillison for reporting this. Closes #20.
2016-02-26 Added link to Mark's Github
2016-03-18 Add power selection resistors R203, R206 as "tie breakers" for VBAT=VIN
    Closes #4
    Bump version V1.5

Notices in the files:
Circuit/ESPlant-Sensors.sch:
Copyright (C) 2015 John Spencer & Angus Gratton
